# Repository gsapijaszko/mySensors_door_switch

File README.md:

# mySensors_door_switch
a simple door/window sensor with Li-Ion battery circuit, nRF24 radio, mySensors network

work in progress, do not expect to much ;)

## Changes
### ver. 1.1
* corrected battery charging schema and pcb
* battery protection changed from DW01 to FS312 
### ver. 1.2, 29.04.2019
* change of ADC pin
* added second reed switch 
* PCB layout correction

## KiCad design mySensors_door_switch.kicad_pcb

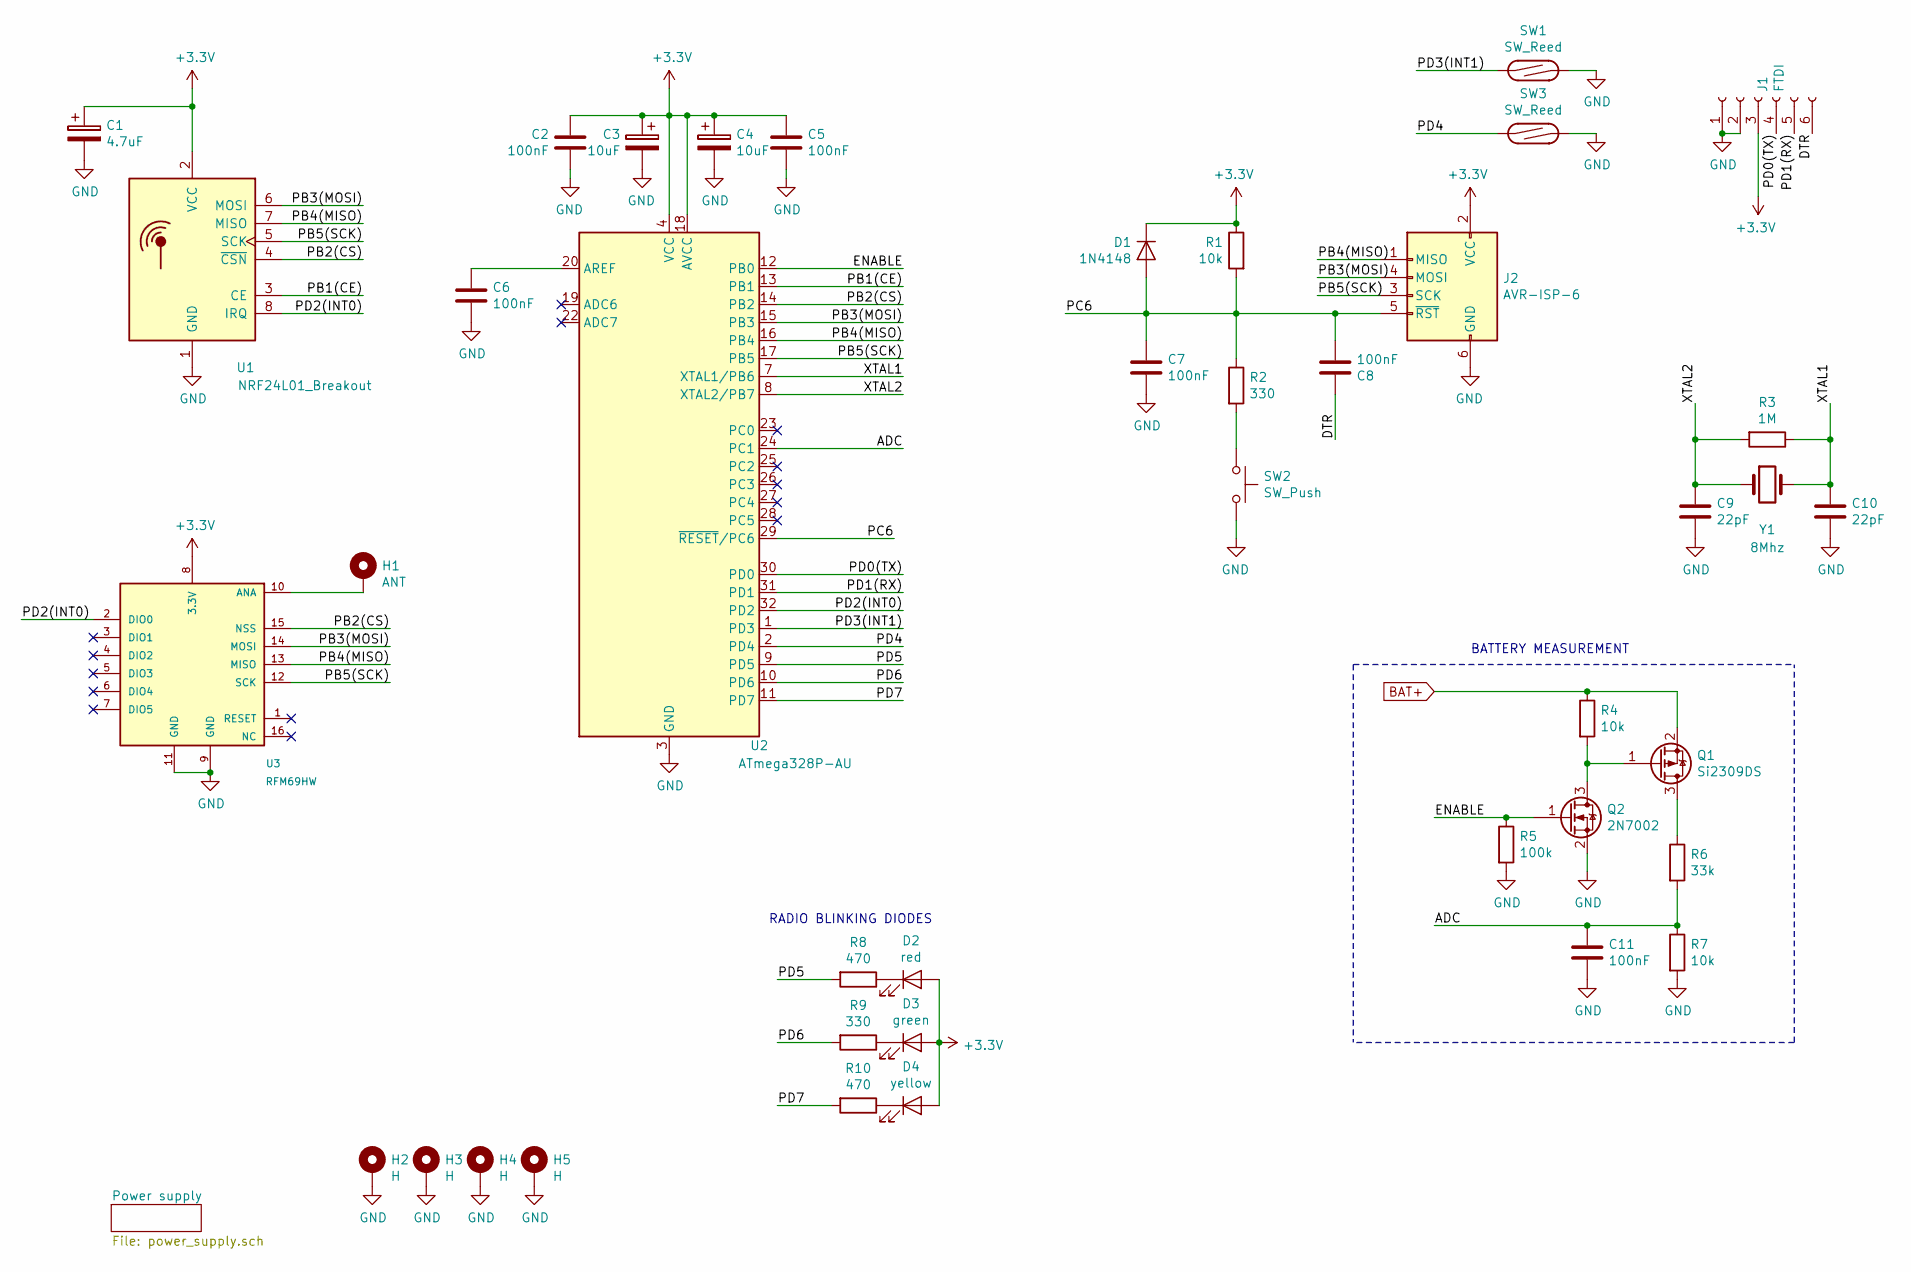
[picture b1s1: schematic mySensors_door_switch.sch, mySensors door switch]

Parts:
C1: 4.7uF; CP_Radial_D5.0mm_P2.50mm
C2, C5, C6, C7, C8, C11: 100nF; C_0805_2012Metric_Pad1.15x1.40mm_HandSolder
C3, C4: 10uF; C_0805_2012Metric_Pad1.15x1.40mm_HandSolder
C9, C10: 22pF; C_1206_3216Metric_Pad1.42x1.75mm_HandSolder
D1: 1N4148; D_DO-34_SOD68_P7.62mm_Horizontal
D2: red; LED_D5.0mm
D3: green; LED_D5.0mm
D4: yellow; LED_D5.0mm
H1: ANT; SolderWirePad_1x01_Drill1.2mm
H2, H3, H4, H5: H; MountingHole_2.7mm_M2.5_Pad_Via
J1: FTDI; PinSocket_1x06_P2.54mm_Vertical
J2: AVR-ISP-6; IDC-Header_2x03_P2.54mm_Vertical
Q1: Si2309DS; SOT-23
Q2: 2N7002; SuperSOT-3
R1, R4, R7: 10k; R_1206_3216Metric_Pad1.42x1.75mm_HandSolder
R2, R9: 330; R_0805_2012Metric_Pad1.15x1.40mm_HandSolder
R3: 1M; R_1206_3216Metric_Pad1.42x1.75mm_HandSolder
R5: 100k; R_1206_3216Metric_Pad1.42x1.75mm_HandSolder
R6: 33k; R_1206_3216Metric_Pad1.42x1.75mm_HandSolder
R8, R10: 470; R_1206_3216Metric_Pad1.42x1.75mm_HandSolder
SW1, SW3: SW_Reed; PinSocket_1x02_P2.54mm_Vertical
SW2: SW_Push; SW_Tactile_SKHH_Angled
U1: NRF24L01_Breakout; nRF24L01_Breakout
U2: ATmega328P-AU; TQFP-32_7x7mm_P0.8mm
U3: RFM69HW; RFM69HW_SMD_ThroughHole_Handsoldering
Y1: 8Mhz; Crystal_HC49-4H_Vertical

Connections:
+3V3: C1.1, C2.1, C3.1, C4.1, C5.1, D1.1 (K), D2.2 (A), D3.2 (A), D4.2 (A), J1.3, J2.2 (VCC), R1.1, U1.2 (VCC), U2.4 (VCC), U2.6 (VCC), U2.18 (AVCC), U3.8 (3.3V); also elsewhere on the board
/ADC: C11.1, R6.2, R7.1, U2.24 (PC1)
/DTR: C8.1, J1.6
/ENABLE: Q2.1 (G), R5.1, U2.12 (PB0)
/PB1(CE): U1.3 (CE), U2.13 (PB1)
/PB2(CS): U1.4 (~CSN), U2.14 (PB2), U3.15 (NSS)
/PB3(MOSI): J2.4 (MOSI), U1.6 (MOSI), U2.15 (PB3), U3.14 (MOSI)
/PB4(MISO): J2.1 (MISO), U1.7 (MISO), U2.16 (PB4), U3.13 (MISO)
/PB5(SCK): J2.3 (SCK), U1.5 (SCK), U2.17 (PB5), U3.12 (SCK)
/PC6: C7.1, C8.2, D1.2 (A), J2.5 (~RST), R1.2, R2.1, U2.29 (~RESET~/PC6)
/PD0(TX): J1.4, U2.30 (PD0)
/PD1(RX): J1.5, U2.31 (PD1)
/PD2(INT0): U1.8 (IRQ), U2.32 (PD2), U3.2 (DIO0)
/PD3(INT1): SW1.1, U2.1 (PD3)
/PD4: SW3.1, U2.2 (PD4)
/PD5: R8.2, U2.9 (PD5)
/PD6: R9.2, U2.10 (PD6)
/PD7: R10.2, U2.11 (PD7)
/XTAL1: C10.1, R3.1, U2.7 (XTAL1/PB6), Y1.2
/XTAL2: C9.1, R3.2, U2.8 (XTAL2/PB7), Y1.1
BAT+: Q1.2 (S), R4.1; also elsewhere on the board
GND: C1.2, C2.2, C3.2, C4.2, C5.2, C6.2, C7.2, C9.2, C10.2, C11.2, H2.1, H3.1, H4.1, H5.1, J1.1, J1.2, J2.6 (GND), Q2.2 (S), R5.2, R7.2, SW1.2, SW2.2, SW3.2, U1.1 (GND), U2.3 (GND), U2.5 (GND), U2.21 (GND), U3.9 (GND), U3.11 (GND); also elsewhere on the board
unnamed: C6.1, U2.20 (AREF)
unnamed: D2.1 (K), R8.1
unnamed: D3.1 (K), R9.1
unnamed: D4.1 (K), R10.1
unnamed: H1.1, U3.10 (ANA)
unnamed: Q1.1 (G), Q2.3 (D), R4.2
unnamed: Q1.3 (D), R6.1
unnamed: R2.2, SW2.1

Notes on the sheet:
RADIO BLINKING DIODES
BATTERY MEASUREMENT

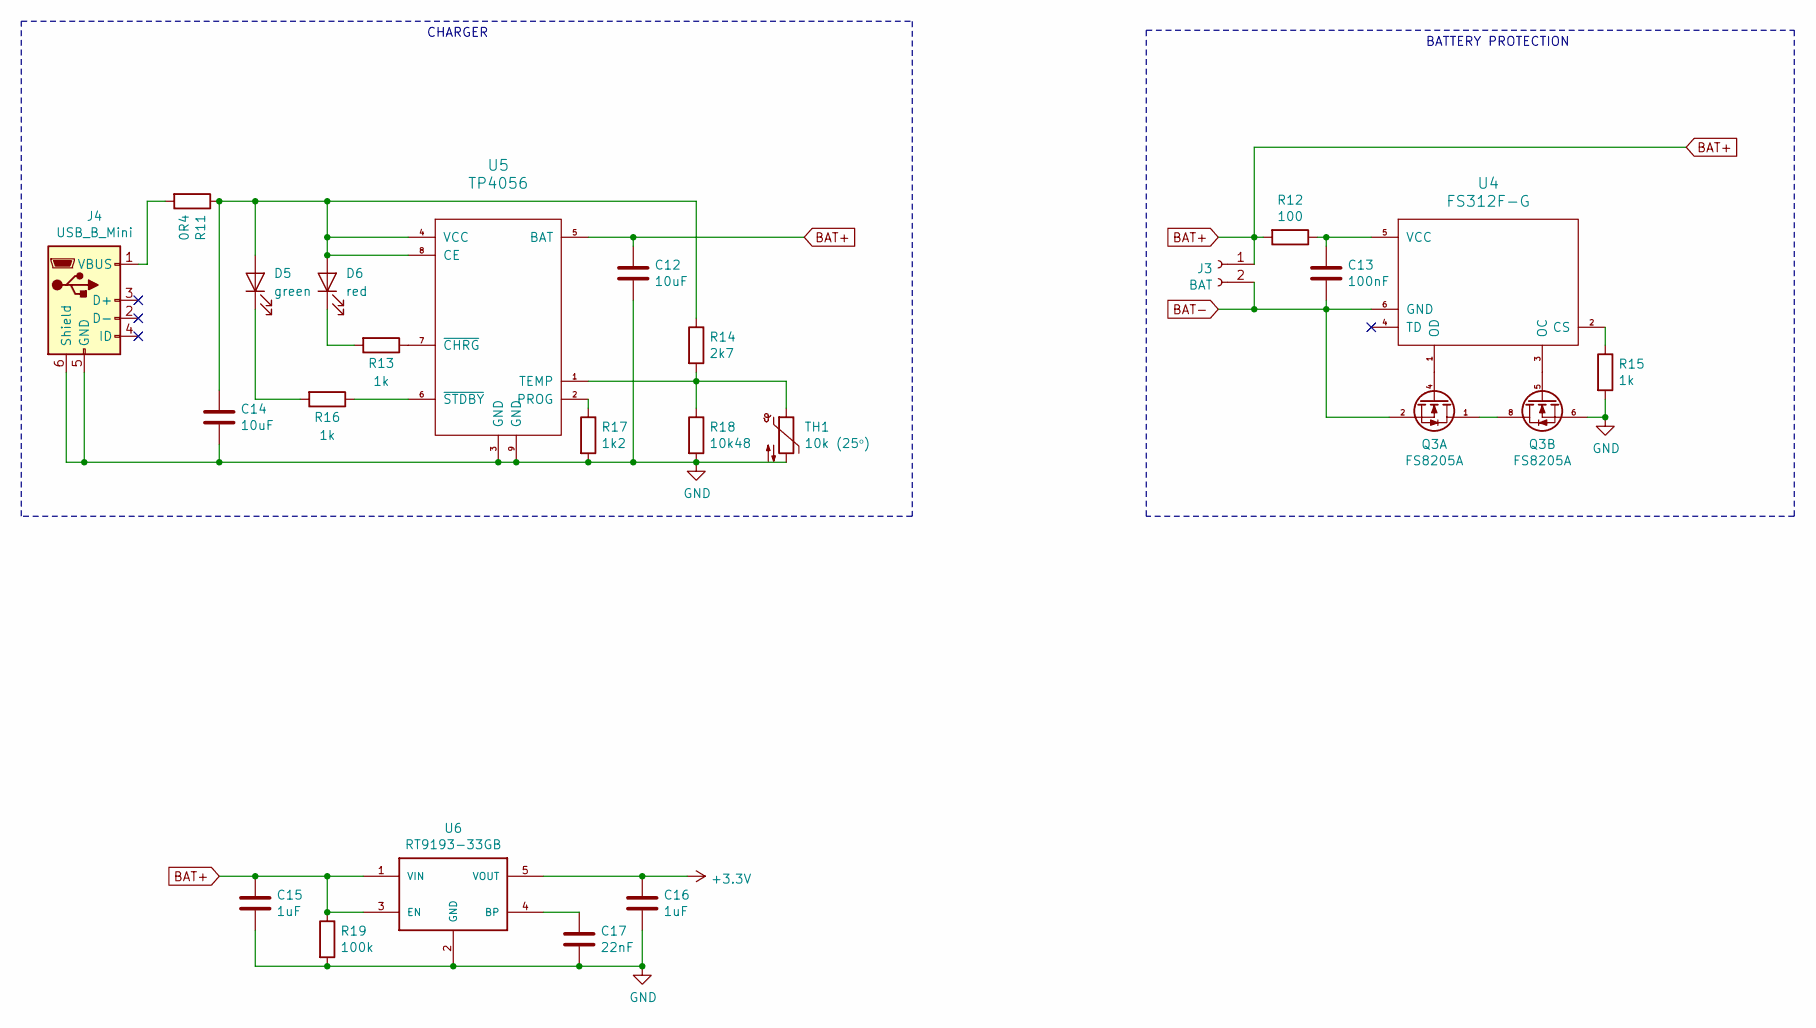
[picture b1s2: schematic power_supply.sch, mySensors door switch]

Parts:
C12, C14: 10uF; C_1206_3216Metric_Pad1.42x1.75mm_HandSolder
C13: 100nF; C_0805_2012Metric_Pad1.15x1.40mm_HandSolder
C15, C16: 1uF; C_0805_2012Metric_Pad1.15x1.40mm_HandSolder
C17: 22nF; C_0805_2012Metric_Pad1.15x1.40mm_HandSolder
D5: green; LED_1210_3225Metric_Pad1.42x2.65mm_HandSolder
D6: red; LED_1210_3225Metric_Pad1.42x2.65mm_HandSolder
J3: BAT; JST_XH_S02B-XH-A_1x02_P2.50mm_Horizontal
J4: USB_B_Mini; USB_Micro-B_Wuerth_629105150521
Q3: FS8205A; TSSOP-8_4.4x3mm_P0.65mm
R11: 0R4; R_1210_3225Metric_Pad1.42x2.65mm_HandSolder
R12: 100; R_1206_3216Metric_Pad1.42x1.75mm_HandSolder
R13, R15, R16: 1k; R_1206_3216Metric_Pad1.42x1.75mm_HandSolder
R14: 2k7; R_1206_3216Metric_Pad1.42x1.75mm_HandSolder
R17: 1k2; R_1206_3216Metric_Pad1.42x1.75mm_HandSolder
R18: 10k48; R_0805_2012Metric_Pad1.15x1.40mm_HandSolder
R19: 100k; R_1206_3216Metric_Pad1.42x1.75mm_HandSolder
TH1: 10k (25ᵒ); R_1218_3246Metric_Pad1.22x4.75mm_HandSolder
U4: FS312F-G; SOT-23-6_Handsoldering
U5: TP4056; HSOP-8-1EP_3.9x4.9mm_P1.27mm_EP2.41x3.1mm_ThermalVias
U6: RT9193-33GB; SOT-23-5_HandSoldering

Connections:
+3V3: C16.1, U6.5 (VOUT); also elsewhere on the board
BAT+: C12.1, C15.1, J3.1, R12.2, R19.1, U5.5 (BAT), U6.1 (VIN), U6.3 (EN); also elsewhere on the board
BAT-: C13.2, J3.2, Q3.2 (S1), U4.6 (GND)
GND: C12.2, C14.2, C15.2, C16.2, C17.2, J4.5 (GND), J4.6 (Shield), Q3.6 (S1), R15.2, R17.2, R18.2, R19.2, TH1.2, U5.3 (GND), U5.9 (GND), U6.2 (GND); also elsewhere on the board
unnamed: C13.1, R12.1, U4.5 (VCC)
unnamed: C14.1, D5.2 (A), D6.2 (A), R11.1, R14.1, U5.4 (VCC), U5.8 (CE)
unnamed: C17.1, U6.4 (BP)
unnamed: D5.1 (K), R16.2
unnamed: D6.1 (K), R13.2
unnamed: J4.1 (VBUS), R11.2
unnamed: Q3.1 (D), Q3.8 (D)
unnamed: Q3.4 (G2), U4.1 (OD)
unnamed: Q3.5 (G2), U4.3 (OC)
unnamed: R13.1, U5.7 (~CHRG)
unnamed: R14.2, R18.1, TH1.1, U5.1 (TEMP)
unnamed: R15.1, U4.2 (CS)
unnamed: R16.1, U5.6 (~STDBY)
unnamed: R17.1, U5.2 (PROG)

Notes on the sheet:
CHARGER
BATTERY PROTECTION

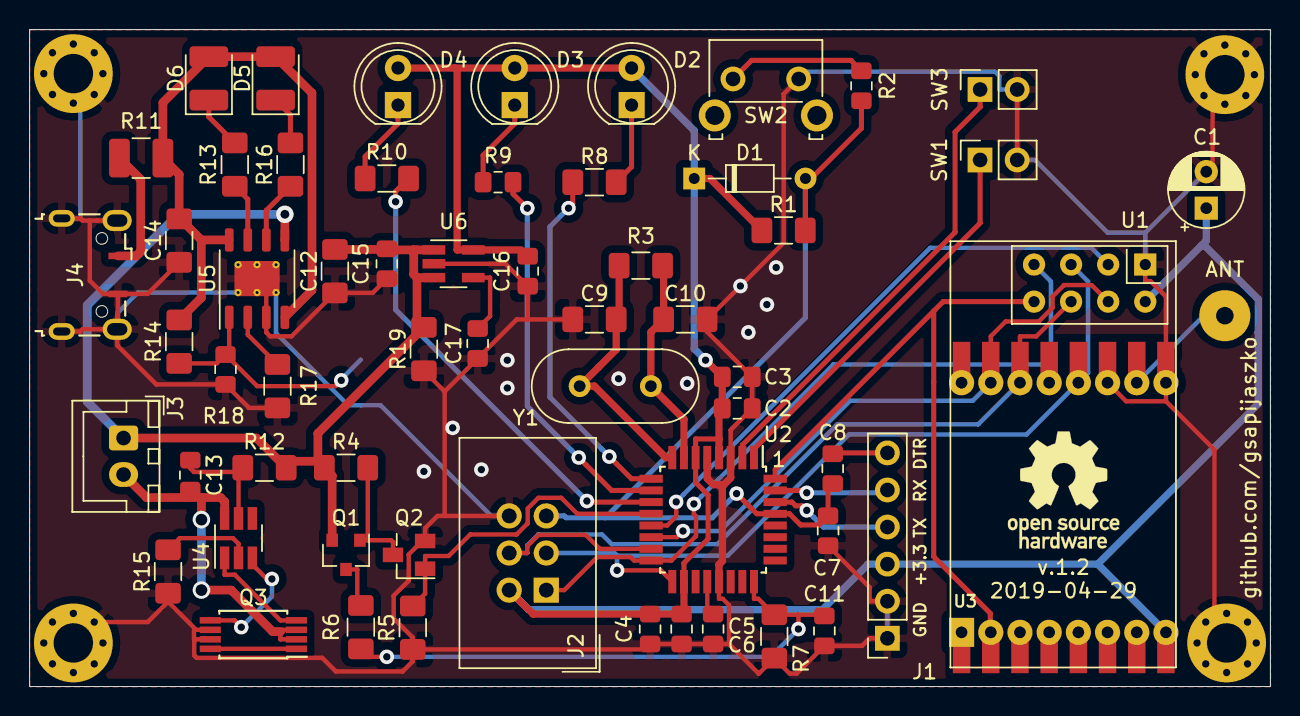
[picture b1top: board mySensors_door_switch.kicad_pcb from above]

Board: 2 copper layers, 85.0 x 45.0 mm, 65 parts (1 on the bottom side), 45 nets.

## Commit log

2019-01-16 Update LICENSE, README.md, and 16 more files...
2019-01-18 Update mySensors_door_switch.kicad_pcb and mySensors_door_switch.kicad_pcb-bak
2019-01-22 Update fp-info-cache, mySensors_door_switch-rescue.dcm, and 2 more files...
2019-01-22 Update fp-info-cache, mySensors_door_switch.kicad_pcb, and mySensors_door_switch.kicad_pcb-bak
2019-01-23 Update fp-info-cache, mySensors_door_switch-cache.lib, and 11 more files...
2019-01-23 Update fp-info-cache, mySensors_door_switch-cache.lib, and 7 more files...
2019-01-24 Update fp-info-cache, mySensors_door_switch-B_Cu.gbr, and 21 more files...
2019-01-24 Update fp-info-cache, mySensors_door_switch-cache.lib, and 13 more files...
2019-01-24 Update mySensors_door_switch.jpg, mySensors_door_switch.kicad_pcb, and 2 more files...
2019-01-26 Update LICENSE, ibom.html, and 24 more files...
2019-01-28 Update fp-info-cache, mySensors_door_switch.dsn, and 4 more files...
2019-01-28 Update mySensors_door_switch-B_Cu.gbr, mySensors_door_switch-B_Mask.gbr, and 9 more files...
2019-01-28 Update fp-info-cache, mySensors_door_switch-B.Cu.gbr, and 19 more files...
2019-02-11 Update fp-info-cache, mySensors_door_switch.jpg, and 2 more files...
2019-02-11 Merge branch 'master' of https://github.com/gsapijaszko/mySensors_door_switch.git
    Conflicts:
    fp-info-cache
2019-02-11 Update ibom.html, mySensors_door_switch.kicad_pcb, and mySensors_door_switch.kicad_pcb-bak
2019-02-14 Update bottom_part.FCStd, bottom_part.FCStd1, and 2 more files...
2019-03-08 Battery charging circuit update
2019-03-09 Update fp-info-cache, mySensors_door_switch-cache.lib, and 12 more files...
2019-03-12 Update README.md, mySensors_door_switch-cache.lib, and 7 more files...
2019-03-13 Update mySensors_door_switch.jpg, mySensors_door_switch.kicad_pcb, and mySensors_door_switch.kicad_pcb-bak
2019-03-13 Update fp-info-cache
2019-03-17 Revert "Revert "Update mySensors_door_switch.jpg, mySensors_door_switch.kicad_pcb, and mySensors_door_switch.kicad_pcb-bak""
    This reverts commit b69a79a09ae4543226fbccfdd42f2f386e584dfe.
2019-03-25 Update fp-info-cache, mySensors_door_switch-cache.lib, and 4 more files...
2019-03-28 Update ibom.html, fp-info-cache, and 4 more files...
2019-03-28 v.1.1, gerbers sent to PCB factory
2019-03-30 Update export.ods, mySensors_door_switch.csv, and 2 more files...
2019-04-18 v.1.2, small PCB changes
2019-04-20 Update fp-info-cache, mySensors_door_switch-B_Cu.gbr, and 17 more files...
2019-04-20 Update fp-info-cache, mySensors_door_switch-B_Cu.gbr, and 19 more files...
2019-04-24 Revert "Update mySensors_door_switch.kicad_pcb, mySensors_door_switch.kicad_pcb-bak, and mySensors_door_switch.pro"
    This reverts commit cb215671e944ab6fd4212124ce306d0e18611652.
    Conflicts:
    mySensors_door_switch.kicad_pcb
2019-04-26 Update fp-info-cache, mySensors_door_switch.bak, and 5 more files...
2019-04-29 Update fp-info-cache, gerbers.zip, and 26 more files...
2019-04-29 v. 1.2 withe gerbers ready to manufacture
